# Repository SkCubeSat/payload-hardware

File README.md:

# payload-hardware
Payload hardware

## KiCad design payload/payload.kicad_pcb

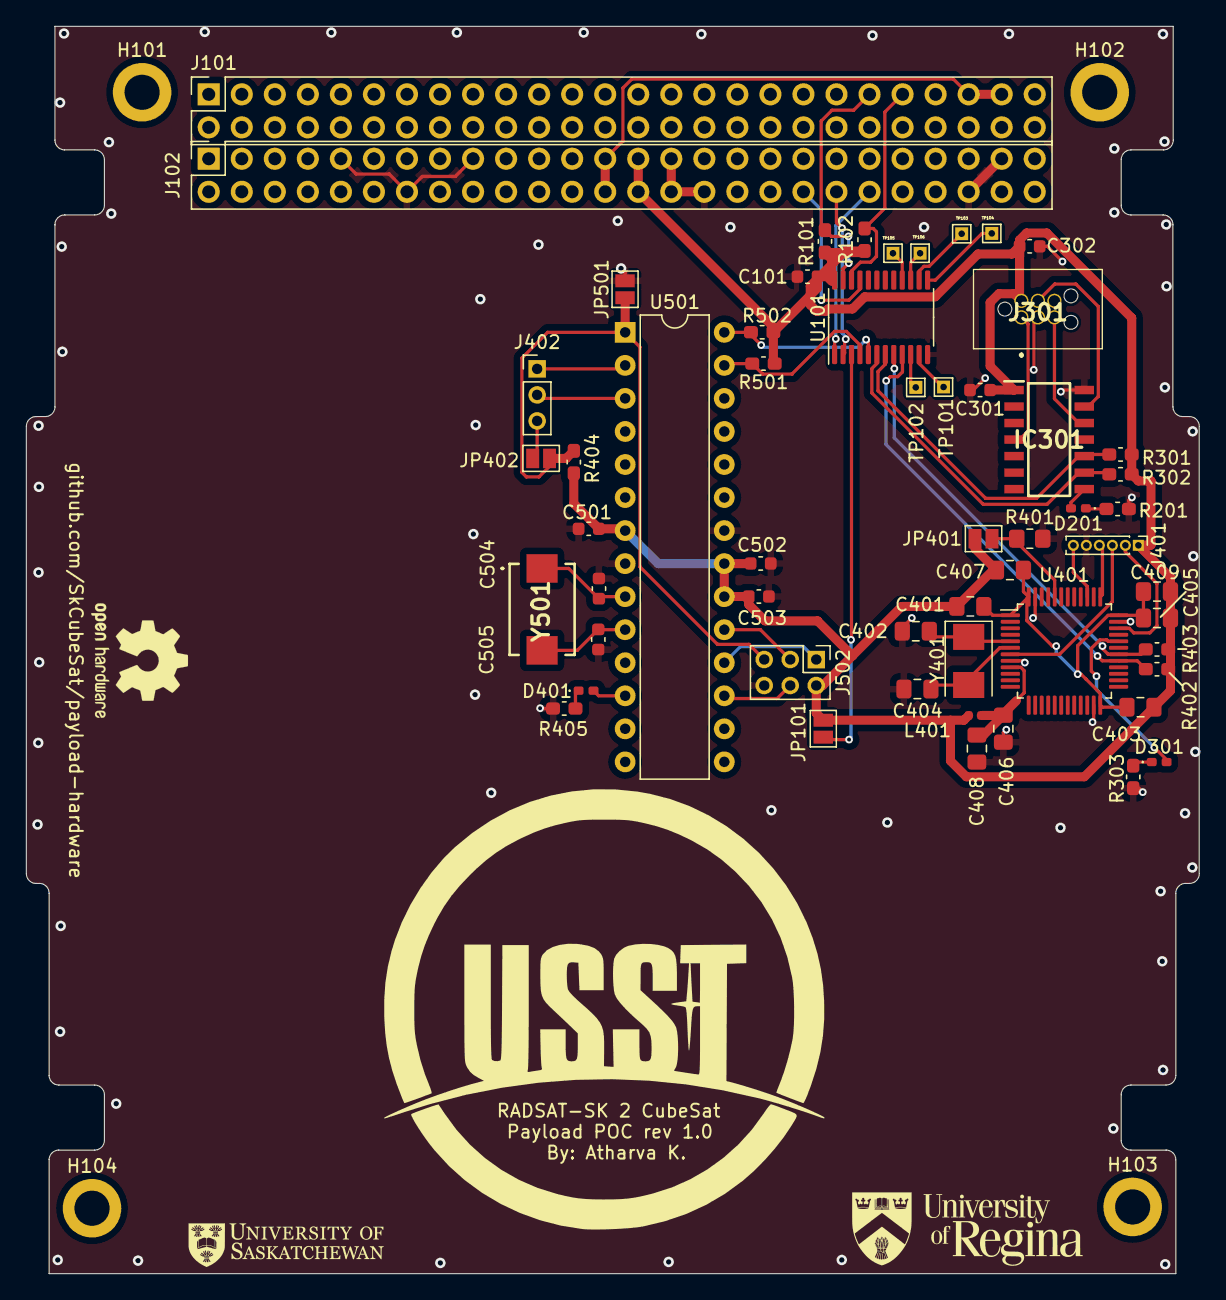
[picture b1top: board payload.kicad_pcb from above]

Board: 2 copper layers, 90.2 x 95.9 mm, 60 parts (0 on the bottom side), 48 nets.

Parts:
C101, C301, C302, C501, C502, C503: 0.1u; C_0603_1608Metric
C401: 4u7; C_0805_2012Metric_Pad1.18x1.45mm_HandSolder
C402, C404: 30p; C_0805_2012Metric_Pad1.18x1.45mm_HandSolder
C403, C405, C407, C408, C409: 100n; C_0805_2012Metric_Pad1.18x1.45mm_HandSolder
C406: 1u; C_0805_2012Metric_Pad1.18x1.45mm_HandSolder
C504, C505: 20pF; C_0603_1608Metric
D201, D301, D401: LED; LED_0402_1005Metric_Pad0.77x0.64mm_HandSolder
H101, H102, H103, H104: MountingHole; MountingHole_2.7mm_M2.5_ISO7380_Pad
IC301: PIC16F1503-I_SL; SOIC127P600X175-14N
J101, J102: Conn_02x26_Odd_Even; PinSocket_2x26_P2.54mm_Vertical
J301: TC2030-MCP-NL-10; TC2030MCPNL10
J401: Conn_01x06_Female; PinHeader_1x06_P1.00mm_Vertical
J402: Conn_01x03; PinHeader_1x03_P2.00mm_Vertical
J502: AVR-ISP-6; PinHeader_2x03_P2.00mm_Vertical
JP101, JP402, JP501: Jumper_2_Open; SolderJumper-2_P1.3mm_Open_Pad1.0x1.5mm
JP401: SolderJumper_2_Open; SolderJumper-2_P1.3mm_Open_Pad1.0x1.5mm
L401: 27n; L_0402_1005Metric
R101, R102, R301, R302, R402, R403, R501, R502: 2k; C_0603_1608Metric_Pad1.08x0.95mm_HandSolder
R201, R303, R405: 1k; C_0603_1608Metric_Pad1.08x0.95mm_HandSolder
R401: 10k; R_0805_2012Metric_Pad1.20x1.40mm_HandSolder
R404: 4k7; C_0603_1608Metric_Pad1.08x0.95mm_HandSolder
TP101, TP102, TP103, TP104, TP105, TP106: TestPoint; TestPoint_THTPad_1.0x1.0mm_Drill0.5mm
U101: PCA9548APW; TSSOP-24_4.4x7.8mm_P0.65mm
U401: STM32F103C8T6; LQFP-48_7x7mm_P0.5mm
U501: ATmega328-P; DIP-28_W7.62mm
Y401: 8MHz; Crystal_SMD_5032-2Pin_5.0x3.2mm
Y501: ECS-100-S-20A-TR; ECS100S20ATR

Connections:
+3.3V: C101.1, C301.1, C302.1, C401.1, C403.1, C405.1, C407.1, C409.1, C501.1, C502.1, C503.1, IC301.1 (VDD), J102.27, J102.28, J301.2 (VDD), J401.1, J502.2 (VCC), JP101.2 (B), JP401.1 (A), L401.1, R101.1, R102.1, R301.1, R302.1, R402.1, R403.1, R404.1, R501.1, R502.1, U101.24 (VCC), U501.7 (VCC), U501.20 (AVCC), U501.21 (AREF)
+3.3VA: C406.1, C408.1, L401.2, U401.9 (VDDA)
+5V: J101.47, J101.49, J102.25, J102.26
/ATMEL/RXD: J402.1, U501.2 (PD0)
/ATMEL/SC0: R502.2, U101.5 (SC0), U501.28 (PC5)
/ATMEL/SD0: R501.2, U101.4 (SD0), U501.27 (PC4)
/ATMEL/TXD: J402.2, U501.3 (PD1)
/ATMEL/XTAL1: C504.1, U501.9 (XTAL1/PB6), Y501.1 (CRYSTAL__2)
/ATMEL/XTAL2: C505.1, U501.10 (XTAL2/PB7), Y501.2 (CRYSTAL__2)
/PIC/SC1: IC301.10 (RC0), R301.2, U101.7 (SC1)
/PIC/SD1: IC301.9 (RC1), R302.2, U101.6 (SD1)
/STM32/HSE_IN: C404.1, U401.6 (PD1), Y401.2
/STM32/HSE_OUT: C402.1, U401.5 (PD0), Y401.1
/STM32/SC2: R402.2, U101.9 (SC2), U401.29 (PA8)
/STM32/SD2: R403.2, U101.8 (SD2), U401.30 (PA9)
/STM32/SWCLK: J401.4, U401.37 (PA14)
/STM32/SWDIO: J401.2, U401.34 (PA13)
/STM32/SWO: J401.6, U401.39 (PB3)
/STM32/nRESET: J401.3, U401.7 (NRST)
GND: C101.2, C301.2, C302.2, C402.2, C404.2, C406.2, C408.2, C501.2, C502.2, C503.2, C504.2, C505.2, IC301.14 (VSS), J102.9, J102.14, J102.17, J102.29, J102.30, J102.32, J102.48, J102.49, J301.3 (GND), J401.5, J502.6 (GND), JP501.2 (B), R201.2, R303.2, R401.2, R405.2, U101.12 (GND), U401.8 (VSSA), U401.23 (VSS), U401.35 (VSS), U401.47 (VSS), U501.8 (GND), U501.22 (GND)
MISO: J502.1 (MISO), U501.18 (PB4)
MOSI: J502.4 (MOSI), U501.17 (PB3)
unnamed: D201.2 (A), IC301.8 (RC2)
unnamed: D201.1 (K), R201.1
unnamed: D301.2 (A), U401.32 (PA11)
unnamed: D301.1 (K), R303.1
unnamed: D401.2 (A), U501.12 (PD6)
unnamed: D401.1 (K), R405.1
unnamed: IC301.13 (RA0/ICSPDAT), J301.4 (PGD(ICSP_DAT))
unnamed: IC301.12 (RA1/ICSPCLK), J301.5 (PGC(ICSP_CLK))
unnamed: IC301.4 (~MCLR/VPP/RA3), J301.1 (MCLR_/_VPP)
unnamed: J102.38, U101.21 (A2)
unnamed: J102.40, U101.2 (A1)
unnamed: J102.42, U101.1 (A0)
unnamed: J402.3, JP402.1 (A)
unnamed: J502.5 (~RST), JP402.2 (B), JP501.1 (A), R404.2, U501.1 (~RESET/PC6)
unnamed: JP101.1 (A), U101.3 (~RESET)
unnamed: JP401.2 (B), R401.1, U401.44 (BOOT0)
unnamed: TP101.1, U101.11 (SC3)
unnamed: TP103.1, U101.14 (SC4)
unnamed: TP105.1, U101.16 (SC5)
unnamed: TP102.1, U101.10 (SD3)
unnamed: TP104.1, U101.13 (SD4)
unnamed: TP106.1, U101.15 (SD5)
unnamed: C401.2, C403.2, C405.2, C407.2, C409.2, U401.1 (VBAT), U401.24 (VDD), U401.36 (VDD), U401.48 (VDD)
SCK: J502.3 (SCK), U501.19 (PB5)
SCL: J101.43, R102.2, U101.22 (SCL)
SDA: J101.41, R101.2, U101.23 (SDA)

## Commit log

2023-07-19 upload rev 1.0 of payload POC rev 1.0
2023-07-21 added LEDs
2023-07-24 added TPs
2023-07-25 push for production
